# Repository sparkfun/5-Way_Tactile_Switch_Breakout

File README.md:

SparkFun 5-Way Tactile Switch Breakout
========================================

[*SparkFun 5-Way Tactile Switch Breakout (BOB-11187)*](https://www.sparkfun.com/products/11187)

This 5-way tactile switch (up, down, left, right, and center click) allows for joystick-like control in a very small package. 
This breadboard-friendly board breaks out all the switch signals, and includes pullup resistors configured so that the outputs read low when pressed, and high otherwise.

Repository Contents
-------------------

* **/Hardware** - Eagle design files (.brd, .sch)
* **/Production** - Production panel files (.brd)

Documentation
--------------
* **[SparkFun Fritzing repo](https://github.com/sparkfun/Fritzing_Parts)** - Fritzing diagrams for SparkFun products.
* **[SparkFun 3D Model repo](https://github.com/sparkfun/3D_Models)** - 3D models of SparkFun products. 

License Information
-------------------
This product is _**open source**_! 

The **hardware** is released under [Creative Commons ShareAlike 4.0 International](https://creativecommons.org/licenses/by-sa/4.0/).

Please use, reuse, and modify these files as you see fit. Please maintain attribution to SparkFun Electronics and release anything derivative under the same license.

Distributed as-is; no warranty is given.

- Your friends at SparkFun.

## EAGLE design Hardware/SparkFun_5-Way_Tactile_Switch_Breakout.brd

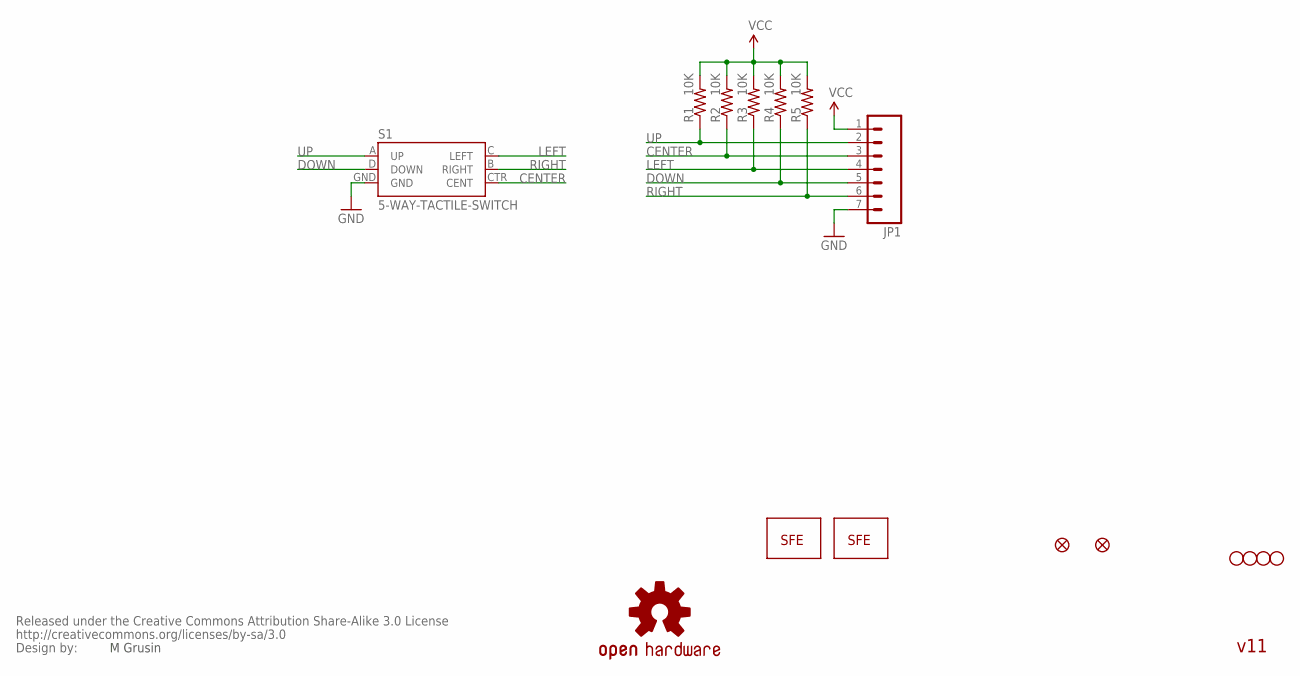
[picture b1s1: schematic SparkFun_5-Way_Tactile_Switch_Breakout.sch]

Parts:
JP1: M07; 1X07
JP2, JP7: FIDUCIALUFIDUCIAL; MICRO-FIDUCIAL
JP3, JP4, JP5, JP6: STAND-OFF
JP9: LOGO-SFESK; SFE-LOGO-FLAME
JP10: LOGO-SFENW2; SFE-NEW-WEB
R1, R2, R3, R4, R5: 10K; 0603-RES
S1: 5-WAY-TACTILE-SWITCH; JOYSTICK_MINI
U$1: OSHW-LOGOS; OSHW-LOGO-S
U$2: CREATIVE_COMMONS

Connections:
CENTER: JP1.3, R2.1, S1.CTR (CENT)
DOWN: JP1.5, R4.1, S1.D (DOWN)
GND: JP1.7, S1.GND
LEFT: JP1.4, R3.1, S1.C (LEFT)
RIGHT: JP1.6, R5.1, S1.B (RIGHT)
UP: JP1.2, R1.1, S1.A (UP)
VCC: JP1.1, R1.2, R2.2, R3.2, R4.2, R5.2

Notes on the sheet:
M Grusin
v11

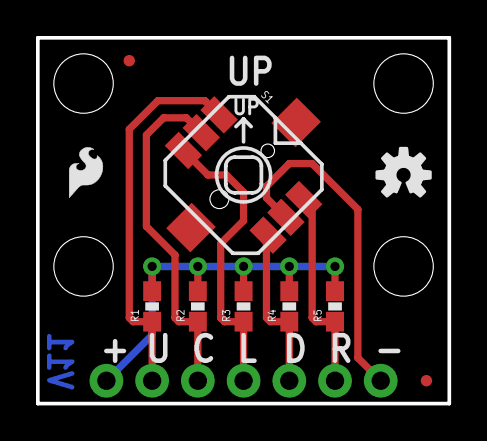
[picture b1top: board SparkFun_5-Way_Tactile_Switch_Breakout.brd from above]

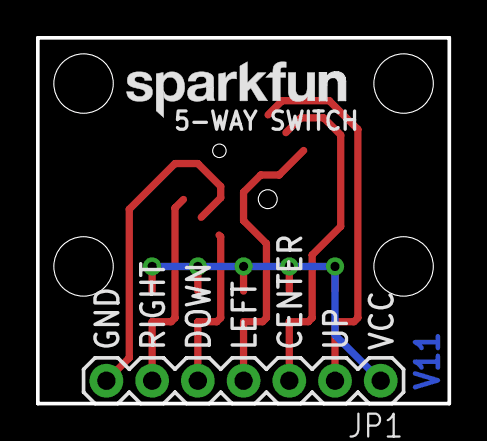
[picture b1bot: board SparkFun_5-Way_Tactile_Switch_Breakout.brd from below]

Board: 2 copper layers, 22.9 x 20.3 mm, 17 parts (2 on the bottom side), 7 nets.

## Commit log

2015-05-07 Adding hardware files

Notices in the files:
parts and their libraries:
SparkFun: Released under the Creative Commons Attribution Share-Alike 3.0 License
SparkFun: http://creativecommons.org/licenses/by-sa/3.0
SparkFun-Electromechanical: Licensing: CC v3.0 Share-Alike You are welcome to use this library for commercial purposes.
